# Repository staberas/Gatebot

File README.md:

WELCOME TO THE GATEBOT PROJECT

HARDWARE REQUIREMENTS:
This projects uses currently a 
- Sipeed Maix Bit with :
  - 4 axis button
  - Servo 
  - A push button
  - An LCD screen & camera (bundled)

FUTURE ENCHANCEMENTS:
- Raspberry Pi will handle the chatbot conversational aspects & wifi communications etc
- a M1N sipeed chip to enchance with more visual recognition or voice activation aspects
- a speaker to hear you AI partner

Currently the device is being debugged using an ESP32 since the USB output is being blocked by the other hardware

This will be filled with documentaion
- TO DO -  

Problems that might arise
- Dont add pcb-files & ai-coprocessor files in your sd card 
- Removed my face biometrics you have to add manually for now  
- some folders might miss 
- you cant yet activate 20class recognition without crashing the facedetection later
- animation speed is slow until i can figure out a way to multithread 
- NOTE: USE THE MINIMUM FIRMWARE
- Rename boot_waifu.py to boot.py

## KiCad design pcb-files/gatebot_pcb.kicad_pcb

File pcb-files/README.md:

version 1 test

_new.zip is the recent pcb design with the 2 uart extended

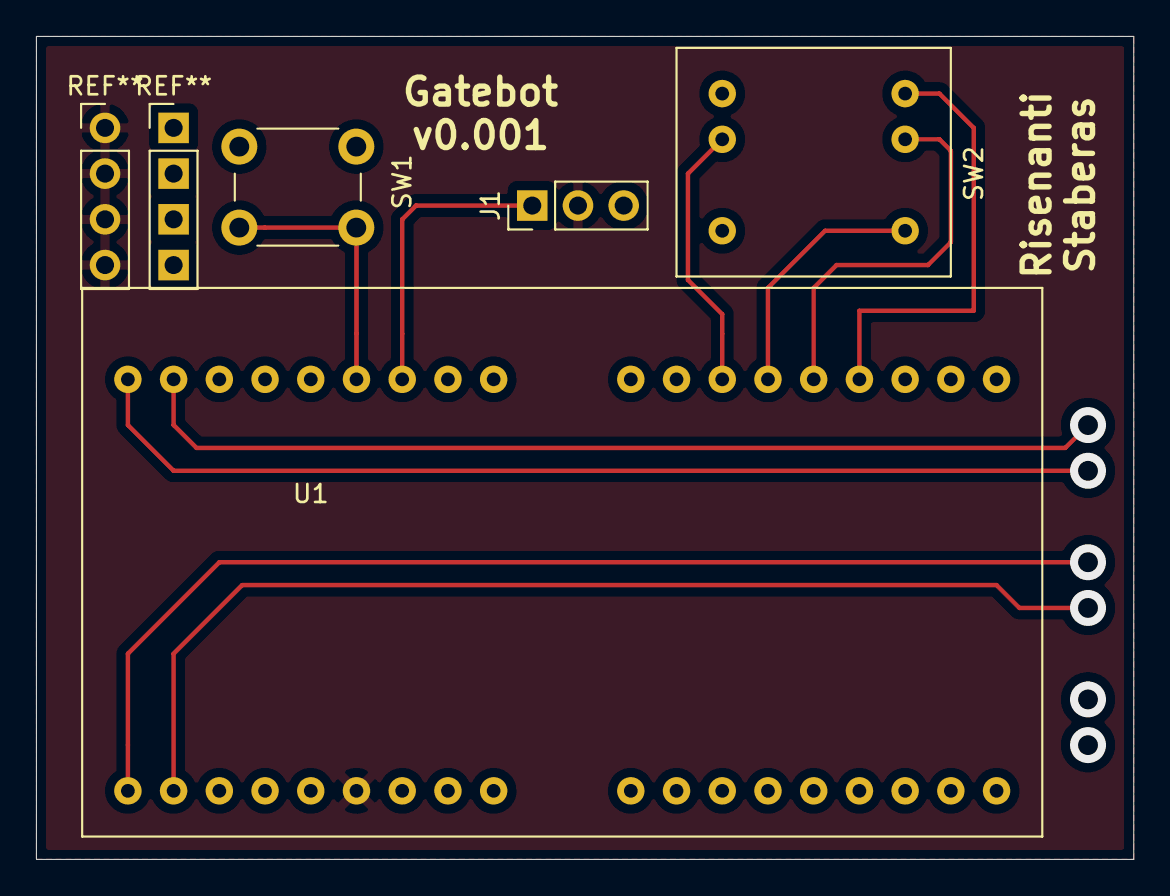
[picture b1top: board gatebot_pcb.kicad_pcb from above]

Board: 2 copper layers, 61.0 x 45.7 mm, 4 parts (0 on the bottom side), 8 nets.

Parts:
J1: Conn_01x03; PinHeader_1x03_P2.54mm_Vertical
SW1: SW_Push; SW_PUSH_6mm
SW2: SW_DIP_x03; weird_6_pin_button
U1: sipeed_maix_bit; sipeeed_maix_bit

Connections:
+5V: J1.2, U1.5v
/BOOT_KEY: SW1.1, U1.16
/ISP_RX: SW2.5, U1.4
/ISP_TX: SW2.6, U1.5
/JTAG_TDO: SW2.4, U1.3
/SERVO_CNTL: J1.1, U1.15
/WIFI_TX: SW2.2, U1.6
GND: J1.3, SW1.2, SW2.3, U1.GND

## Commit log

2020-10-22 Add files via upload
    M1N settings for kflash_gui (for yolo py)
    20class.kmodel @ 0x500000
    board: sipeed Maixduino
    burn to Flash
2020-10-23 Update qrwithcolor.py
    UART extension on 15 , 7 pins
2020-10-23 Update 20YOL.py
    uart read extra info (still not in json)
2020-10-23 Update 20YOL.py
    added json decoder
2020-10-26 Update 20YOL.py
    timer before start
2020-10-27 Update 20YOL.py
    2uart
2020-10-31 Update boot_waifu.py
    vision synthesis uart data
2020-10-31 Update 20YOL.py
    cleanup TODO: rename to vision-synthesis
2020-10-31 Update boot_waifu.py
    fixes and imported ujson
2020-11-04 skin color & darkness tracking demo
2020-11-05 Update qrwithcolor.py
    update
2022-11-22 Adding tarfile member sanitization to extractall()
